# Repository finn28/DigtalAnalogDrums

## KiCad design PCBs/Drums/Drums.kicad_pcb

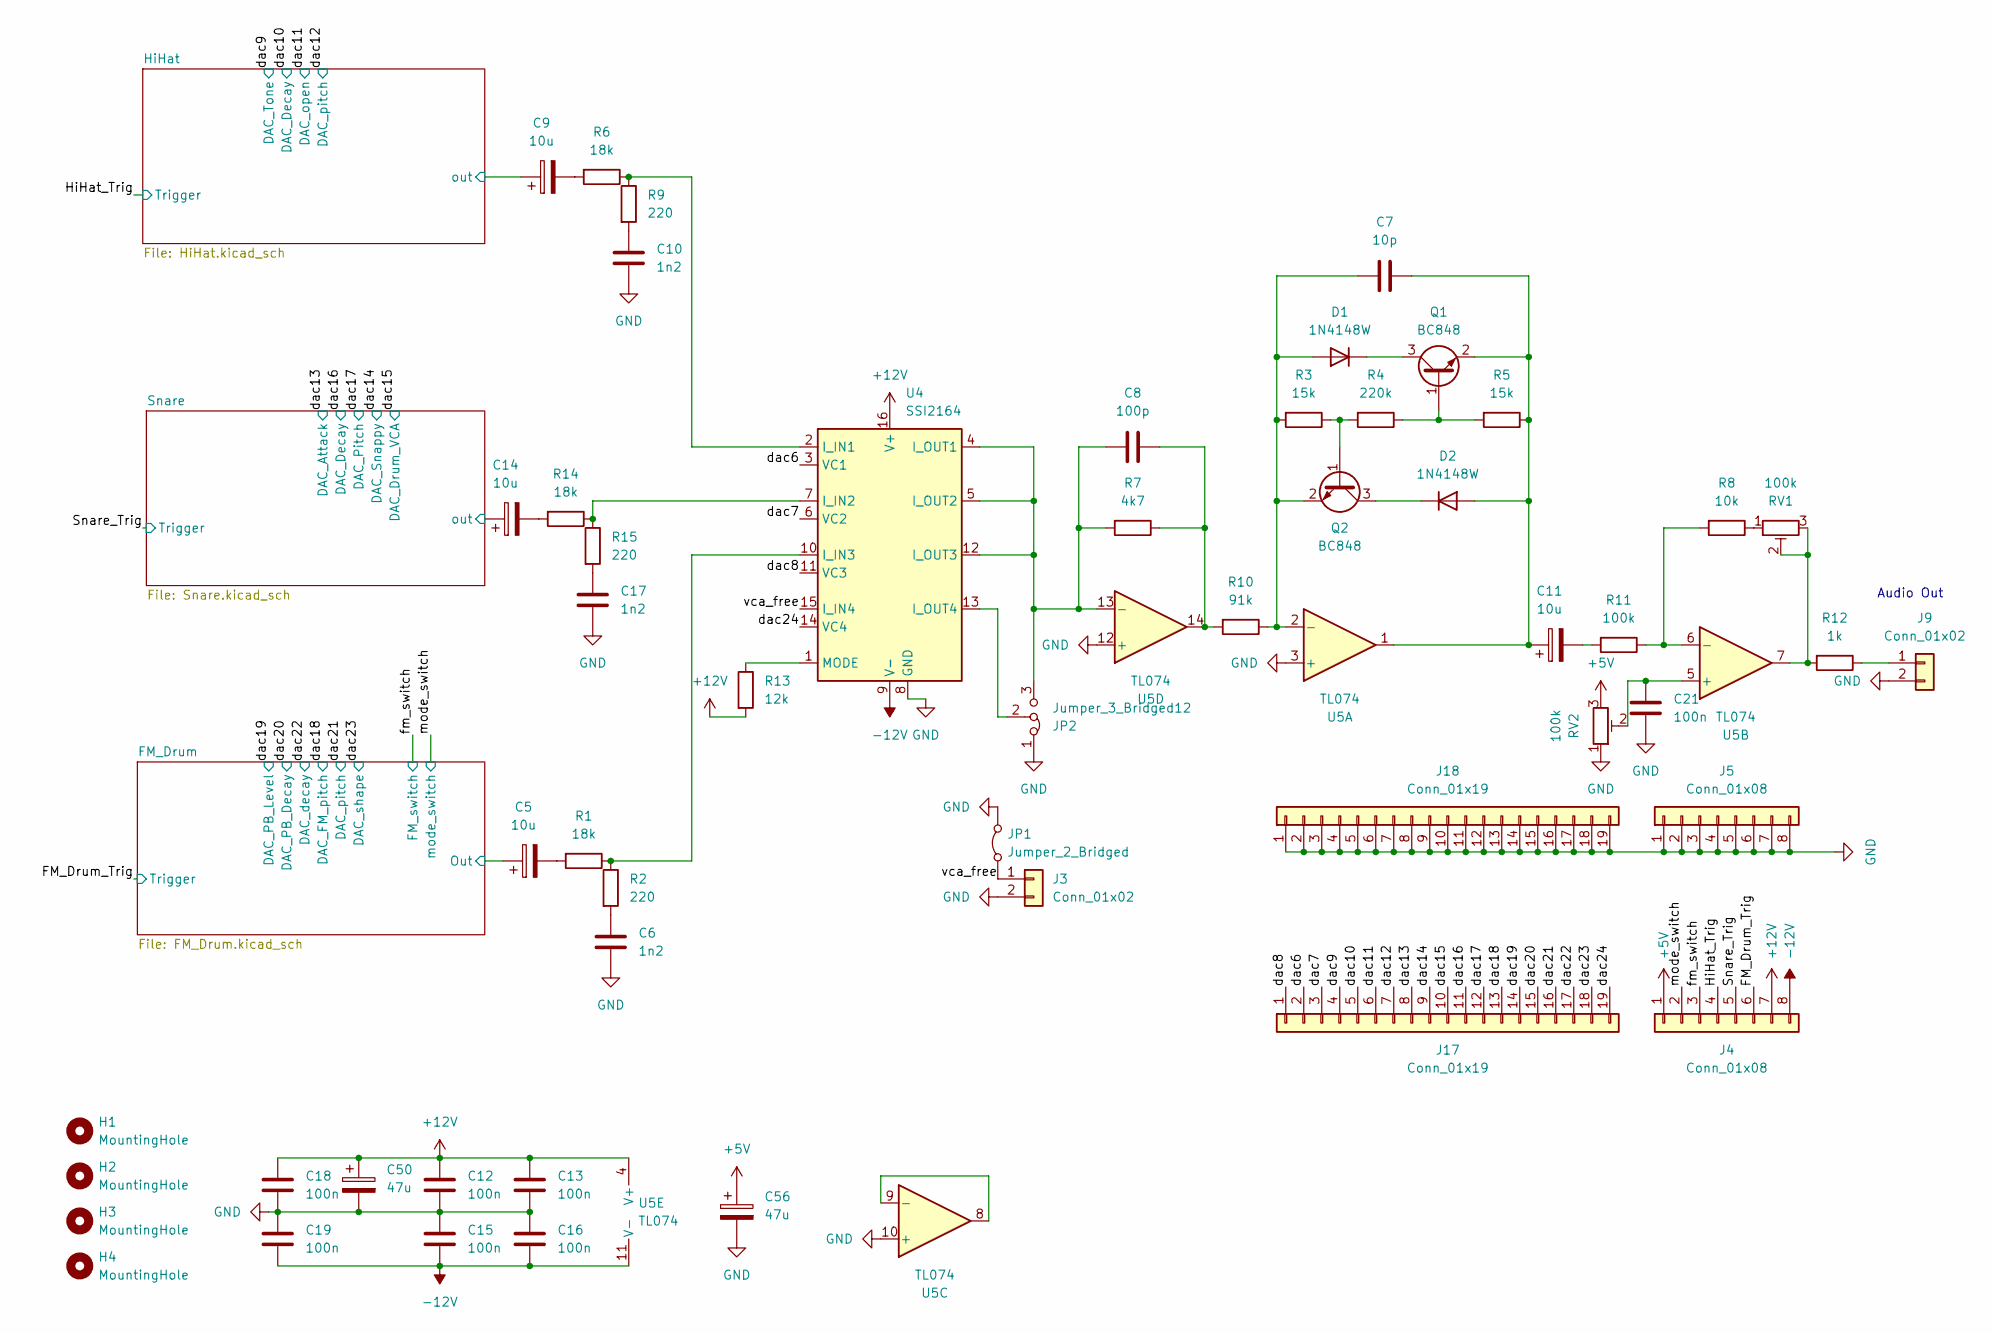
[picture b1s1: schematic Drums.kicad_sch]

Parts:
C5, C9, C11, C14: 10u; CP_Elec_5x5.9
C6, C10, C17: 1n2; C_0805_2012Metric
C7: 10p; C_0805_2012Metric
C8: 100p; C_0805_2012Metric
C12, C13, C15, C16, C18, C19, C21: 100n; C_0402_1005Metric_Pad0.74x0.62mm_HandSolder
C50, C56: 47u; CP_Elec_5x5.9
D1, D2: 1N4148W; D_SOD-123
H1, H2, H3, H4: MountingHole; MountingHole_3.2mm_M3
J3, J9: Conn_01x02; PinHeader_1x02_P2.54mm_Vertical
J4, J5: Conn_01x08; SMD Con8
J17, J18: Conn_01x19; SMD Con19
JP1: Jumper_2_Bridged; SolderJumper-2_P1.3mm_Open_TrianglePad1.0x1.5mm
JP2: Jumper_3_Bridged12; SolderJumper-3_P2.0mm_Open_TrianglePad1.0x1.5mm
Q1, Q2: BC848; SOT-23
R1, R6, R14: 18k; R_0805_2012Metric_Pad1.20x1.40mm_HandSolder
R2, R9, R15: 220; R_0805_2012Metric_Pad1.20x1.40mm_HandSolder
R3, R5: 15k; R_0805_2012Metric_Pad1.20x1.40mm_HandSolder
R4: 220k; R_0805_2012Metric_Pad1.20x1.40mm_HandSolder
R7: 4k7; R_0805_2012Metric_Pad1.20x1.40mm_HandSolder
R8: 10k; R_0805_2012Metric_Pad1.20x1.40mm_HandSolder
R10: 91k; R_0805_2012Metric_Pad1.20x1.40mm_HandSolder
R11: 100k; R_0805_2012Metric_Pad1.20x1.40mm_HandSolder
R12: 1k; R_0805_2012Metric_Pad1.20x1.40mm_HandSolder
R13: 12k; R_0805_2012Metric_Pad1.20x1.40mm_HandSolder
RV1, RV2: 100k; Potentiometer_Bourns_3296W_Vertical
U4: SSI2164; SOIC-16_3.9x9.9mm_P1.27mm
U5: TL074; TSSOP-14_4.4x5mm_P0.65mm

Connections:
+5V: C56.1, J4.1, RV2.3; also elsewhere on the board
+12V: C12.2, C13.2, C18.2, C50.1, J4.7, R13.2, U4.16 (V+), U5.4 (V+); also elsewhere on the board
-12V: C15.1, C16.1, C19.1, J4.8, U4.9 (V-), U5.11 (V-); also elsewhere on the board
/FM_Drum/Out: C5.1; also elsewhere on the board
/FM_Drum_Trig: J4.6; also elsewhere on the board
/HiHat/out: C9.1; also elsewhere on the board
/HiHat_Trig: J4.4; also elsewhere on the board
/Snare/out: C14.1; also elsewhere on the board
/Snare_Trig: J4.5; also elsewhere on the board
/dac6: J17.2, U4.3 (VC1)
/dac7: J17.3, U4.6 (VC2)
/dac8: J17.1, U4.11 (VC3)
/dac9: J17.4; also elsewhere on the board
/dac10: J17.5; also elsewhere on the board
/dac11: J17.6; also elsewhere on the board
/dac12: J17.7; also elsewhere on the board
/dac13: J17.8; also elsewhere on the board
/dac14: J17.9; also elsewhere on the board
/dac15: J17.10; also elsewhere on the board
/dac16: J17.11; also elsewhere on the board
/dac17: J17.12; also elsewhere on the board
/dac18: J17.13; also elsewhere on the board
/dac19: J17.14; also elsewhere on the board
/dac20: J17.15; also elsewhere on the board
/dac21: J17.16; also elsewhere on the board
/dac22: J17.17; also elsewhere on the board
/dac23: J17.18; also elsewhere on the board
/dac24: J17.19, U4.14 (VC4)
/fm_switch: J4.3; also elsewhere on the board
/mode_switch: J4.2; also elsewhere on the board
/vca_free: J3.1, JP1.1 (A), U4.15 (I_IN4)
GND: C6.1, C10.1, C12.1, C13.1, C15.2, C16.2, C17.1, C18.1, C19.2, C21.1, C50.2, C56.2, J3.2, J5.1, J5.2, J5.3, J5.4, J5.5, J5.6, J5.7, J5.8, J9.2, J18.1, J18.2, J18.3, J18.4, J18.5, J18.6, J18.7, J18.8, J18.9, J18.10, J18.11, J18.12, J18.13, J18.14, J18.15, J18.16, J18.17, J18.18, J18.19, JP1.2 (B), JP2.1 (A), RV2.1, U4.8 (GND), U5.3 (+), U5.10 (+), U5.12 (+); also elsewhere on the board
unnamed: C5.2, R1.2
unnamed: C6.2, R2.2
unnamed: C8.2, R7.1, R10.2, U5.14
unnamed: C9.2, R6.2
unnamed: C10.2, R9.2
unnamed: C11.2, R11.2
unnamed: C14.2, R14.2
unnamed: C17.2, R15.2
unnamed: C7.1, D1.2 (A), Q2.2 (E), R3.2, R10.1, U5.2 (-)
unnamed: D1.1 (K), Q1.3 (C)
unnamed: C7.2, C11.1, D2.2 (A), Q1.2 (E), R5.1, U5.1
unnamed: D2.1 (K), Q2.3 (C)
unnamed: J9.1, R12.1
unnamed: C8.1, JP2.3 (B), R7.2, U4.4 (I_OUT1), U4.5 (I_OUT2), U4.12 (I_OUT3), U5.13 (-)
unnamed: JP2.2 (C), U4.13 (I_OUT4)
unnamed: Q1.1 (B), R4.1, R5.2
unnamed: Q2.1 (B), R3.1, R4.2
unnamed: R8.1, RV1.1
unnamed: R12.2, RV1.2, RV1.3, U5.7
unnamed: R6.1, R9.1, U4.2 (I_IN1)
unnamed: R14.1, R15.1, U4.7 (I_IN2)
unnamed: R1.1, R2.1, U4.10 (I_IN3)
unnamed: R13.1, U4.1 (MODE)
unnamed: C21.2, RV2.2, U5.5 (+)
unnamed: R8.2, R11.1, U5.6 (-)
unnamed: U5.8, U5.9 (-)

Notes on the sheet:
Audio Out

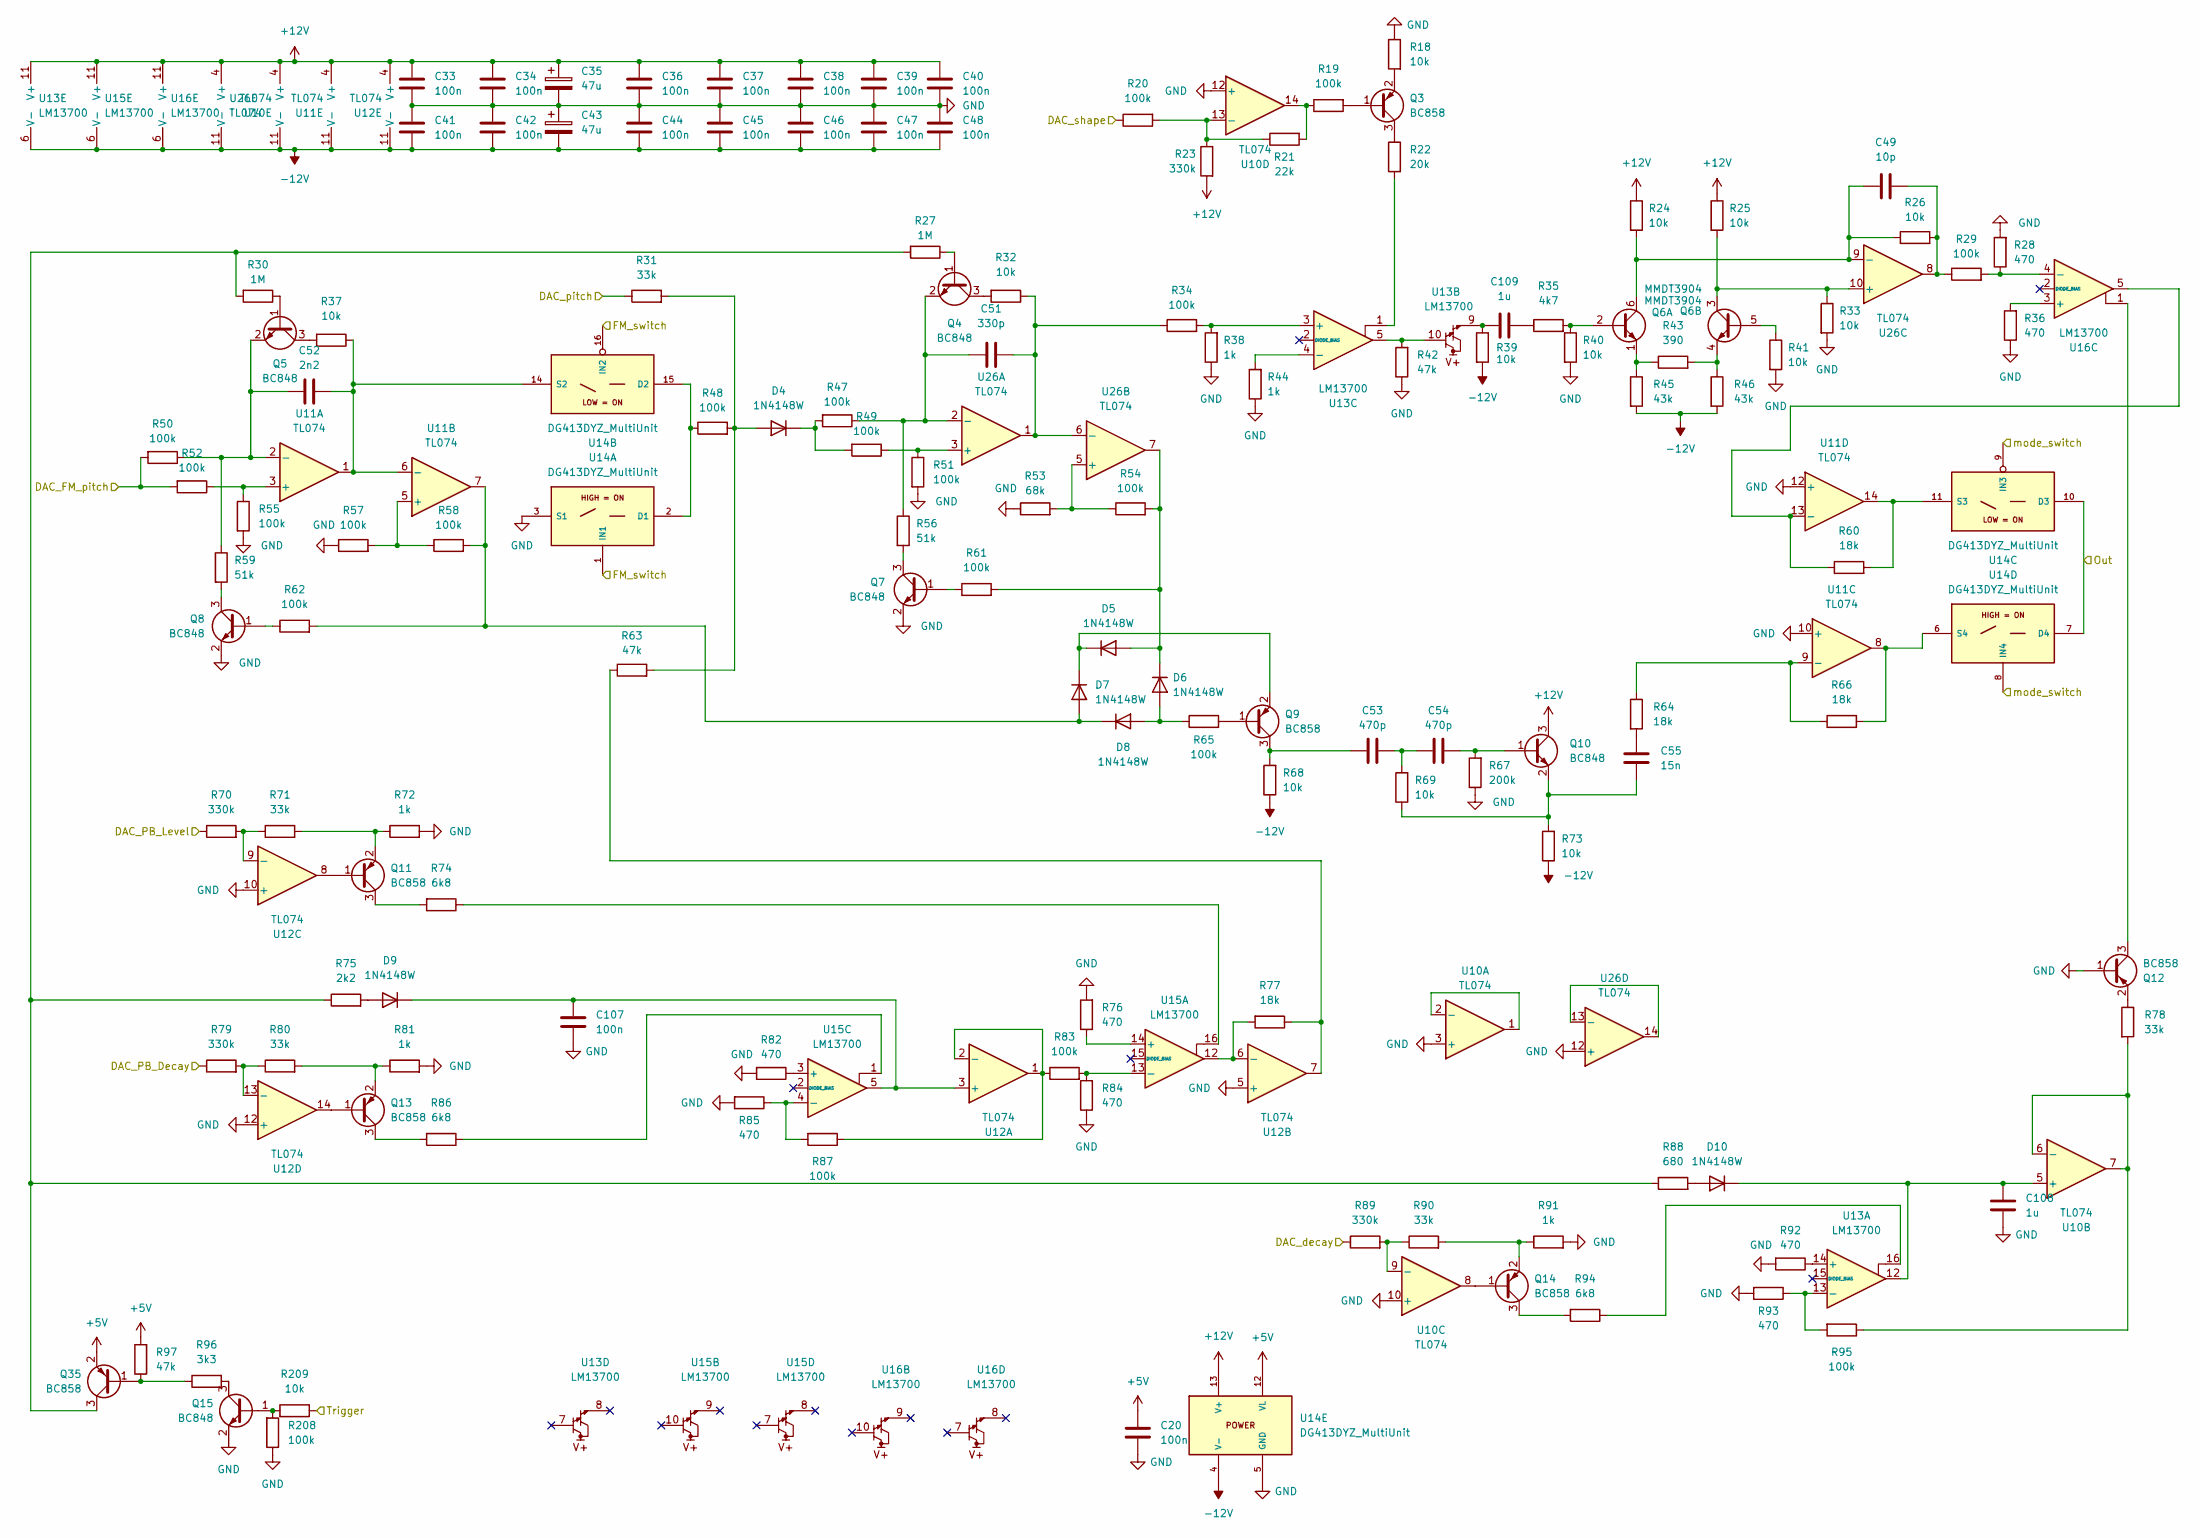
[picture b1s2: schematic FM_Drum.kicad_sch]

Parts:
C20, C33, C34, C36, C37, C38, C39, C40, C41, C42, C44, C45, C46, C47, C48: 100n; C_0402_1005Metric_Pad0.74x0.62mm_HandSolder
C35, C43: 47u; CP_Elec_5x5.9
C49: 10p; C_0805_2012Metric
C51: 330p; C_Rect_L7.2mm_W4.5mm_P5.00mm_FKS2_FKP2_MKS2_MKP2
C52: 2n2; C_Disc_D7.0mm_W2.5mm_P5.00mm
C53, C54: 470p; C_Rect_L7.2mm_W4.5mm_P5.00mm_FKS2_FKP2_MKS2_MKP2
C55: 15n; C_Disc_D7.0mm_W2.5mm_P5.00mm
C107: 100n; C_Rect_L7.2mm_W5.0mm_P5.00mm
C108, C109: 1u; C_Rect_L7.2mm_W5.0mm_P5.00mm
D4, D5, D6, D7, D8, D9, D10: 1N4148W; D_SOD-123
Q3, Q9, Q11, Q12, Q13, Q14, Q35: BC858; SOT-23
Q4, Q5, Q7, Q8, Q10, Q15: BC848; SOT-23
Q6: MMDT3904; SOT-363_SC-70-6
R18, R24, R25, R26, R32, R33, R37, R39, R40, R41, R68, R69, R73, R209: 10k; R_0805_2012Metric_Pad1.20x1.40mm_HandSolder
R19, R20, R29, R34, R47, R48, R49, R50, R51, R52, R54, R55, R57, R58, R61, R62, R65, R83, R87, R95, R208: 100k; R_0805_2012Metric_Pad1.20x1.40mm_HandSolder
R21: 22k; R_0805_2012Metric_Pad1.20x1.40mm_HandSolder
R22: 20k; R_0805_2012Metric_Pad1.20x1.40mm_HandSolder
R23, R70, R79, R89: 330k; R_0805_2012Metric_Pad1.20x1.40mm_HandSolder
R27, R30: 1M; R_0805_2012Metric_Pad1.20x1.40mm_HandSolder
R28, R36, R76, R82, R84, R85, R92, R93: 470; R_0805_2012Metric_Pad1.20x1.40mm_HandSolder
R31, R71, R78, R80, R90: 33k; R_0805_2012Metric_Pad1.20x1.40mm_HandSolder
R35: 4k7; R_0805_2012Metric_Pad1.20x1.40mm_HandSolder
R38, R44, R72, R81, R91: 1k; R_0805_2012Metric_Pad1.20x1.40mm_HandSolder
R42, R63, R97: 47k; R_0805_2012Metric_Pad1.20x1.40mm_HandSolder
R43: 390; R_0805_2012Metric_Pad1.20x1.40mm_HandSolder
R45, R46: 43k; R_0805_2012Metric_Pad1.20x1.40mm_HandSolder
R53: 68k; R_0805_2012Metric_Pad1.20x1.40mm_HandSolder
R56, R59: 51k; R_0805_2012Metric_Pad1.20x1.40mm_HandSolder
R60, R64, R66, R77: 18k; R_0805_2012Metric_Pad1.20x1.40mm_HandSolder
R67: 200k; R_0805_2012Metric_Pad1.20x1.40mm_HandSolder
R74, R86, R94: 6k8; R_0805_2012Metric_Pad1.20x1.40mm_HandSolder
R75: 2k2; R_0805_2012Metric_Pad1.20x1.40mm_HandSolder
R88: 680; R_0805_2012Metric_Pad1.20x1.40mm_HandSolder
R96: 3k3; R_0805_2012Metric_Pad1.20x1.40mm_HandSolder
U10, U11, U12, U26: TL074; TSSOP-14_4.4x5mm_P0.65mm
U13, U15, U16: LM13700; SOIC-16_3.9x9.9mm_P1.27mm
U14: DG413DYZ_MultiUnit; SOIC-16_3.9x9.9mm_P1.27mm; Mouser 968-DG413DYZ

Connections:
+5V: C20.2, Q35.2 (E), R97.2, U14.12 (VL); also elsewhere on the board
+12V: C33.1, C34.1, C35.1, C36.1, C37.1, C38.1, C39.1, C40.1, Q10.3 (C), R23.2, R24.1, R25.1, U10.4 (V+), U11.4 (V+), U12.4 (V+), U13.11 (V+), U14.13 (V+), U15.11 (V+), U16.11 (V+), U26.4 (V+); also elsewhere on the board
-12V: C41.2, C42.2, C43.2, C44.2, C45.2, C46.2, C47.2, C48.2, R39.2, R45.2, R46.2, R68.1, R73.1, U10.11 (V-), U11.11 (V-), U12.11 (V-), U13.6 (V-), U14.4 (V-), U15.6 (V-), U16.6 (V-), U26.11 (V-); also elsewhere on the board
/FM_Drum/Out: U14.7 (D4), U14.10 (D3); also elsewhere on the board
/FM_Drum_Trig: R209.1; also elsewhere on the board
/dac18: R50.2, R52.2; also elsewhere on the board
/dac19: R70.1; also elsewhere on the board
/dac20: R79.1; also elsewhere on the board
/dac21: R31.1; also elsewhere on the board
/dac22: R89.1; also elsewhere on the board
/dac23: R20.1; also elsewhere on the board
/fm_switch: U14.1 (IN1), U14.16 (IN2); also elsewhere on the board
/mode_switch: U14.8 (IN4), U14.9 (IN3); also elsewhere on the board
GND: C20.1, C33.2, C34.2, C35.2, C36.2, C37.2, C38.2, C39.2, C40.2, C41.1, C42.1, C43.1, C44.1, C45.1, C46.1, C47.1, C48.1, C107.2, C108.2, Q7.2 (E), Q8.2 (E), Q12.1 (B), Q15.2 (E), R18.1, R28.2, R33.2, R36.1, R38.1, R40.2, R41.2, R42.1, R44.1, R51.2, R53.1, R55.2, R57.1, R67.1, R72.2, R76.2, R81.2, R82.2, R84.1, R85.2, R91.2, R92.2, R93.2, R208.1, U10.3 (+), U10.10 (+), U10.12 (+), U11.10 (+), U11.12 (+), U12.5 (+), U12.10 (+), U12.12 (+), U14.3 (S1), U14.5 (GND), U26.12 (+); also elsewhere on the board
unnamed: C49.2, R26.2, R29.1, U26.8
unnamed: C53.1, C54.2, R69.2
unnamed: C55.1, R64.2
unnamed: C109.1, R39.1, U13.9
unnamed: C109.2, R35.1
unnamed: D4.2 (A), R31.2, R48.2, R63.2
unnamed: D4.1 (K), R47.2, R49.2
unnamed: D5.2 (A), D6.1 (K), R54.2, R61.2, U26.7
unnamed: D5.1 (K), D7.1 (K), Q9.2 (E)
unnamed: D6.2 (A), D8.2 (A), R65.1
unnamed: D7.2 (A), D8.1 (K), R58.2, R62.2, U11.7
unnamed: D9.2 (A), R75.2
unnamed: C107.1, D9.1 (K), U12.3 (+), U15.5
unnamed: D10.2 (A), R88.2
unnamed: C108.1, D10.1 (K), U10.5 (+), U13.12
unnamed: Q3.1 (B), R19.2
unnamed: Q3.3 (C), R22.1
unnamed: Q3.2 (E), R18.2
unnamed: Q4.1 (B), R27.1
unnamed: Q4.3 (C), R32.2
unnamed: C51.2, Q4.2 (E), R47.1, R56.1, U26.2 (-)
unnamed: Q5.1 (B), R30.1
unnamed: Q5.3 (C), R37.2
unnamed: C52.2, Q5.2 (E), R50.1, R59.1, U11.2 (-)
unnamed: Q6.2 (B1), R35.2, R40.1
unnamed: C49.1, Q6.6 (C1), R24.2, R26.1, U26.9 (-)
unnamed: Q6.1 (E1), R43.1, R45.1
unnamed: Q6.5 (B2), R41.1
unnamed: Q6.3 (C2), R25.2, R33.1, U26.10 (+)
unnamed: Q6.4 (E2), R43.2, R46.1
unnamed: Q7.1 (B), R61.1
unnamed: Q7.3 (C), R56.2
unnamed: Q8.1 (B), R62.1
unnamed: Q8.3 (C), R59.2
unnamed: Q9.1 (B), R65.2
unnamed: C53.2, Q9.3 (C), R68.2
unnamed: C54.1, Q10.1 (B), R67.2
unnamed: C55.2, Q10.2 (E), R69.1, R73.2
unnamed: Q11.1 (B), U12.8
unnamed: Q11.3 (C), R74.2
unnamed: Q11.2 (E), R71.2, R72.1
unnamed: Q12.3 (C), U16.1
unnamed: Q12.2 (E), R78.1
unnamed: Q13.1 (B), U12.14
unnamed: Q13.3 (C), R86.2
unnamed: Q13.2 (E), R80.2, R81.1
unnamed: Q14.1 (B), U10.8
unnamed: Q14.3 (C), R94.2
unnamed: Q14.2 (E), R90.2, R91.1
unnamed: Q15.1 (B), R208.2, R209.2
unnamed: Q15.3 (C), R96.2
unnamed: Q35.1 (B), R96.1, R97.1
unnamed: Q35.3 (C), R27.2, R30.2, R75.1, R88.1
unnamed: R19.1, R21.2, U10.14
unnamed: R22.2, U13.1
unnamed: R42.2, U13.5, U13.10
unnamed: R63.1, R77.1, U12.7
unnamed: R74.1, U15.16
unnamed: R86.1, U15.1
unnamed: R94.1, U13.16
unnamed: U10.1, U10.2 (-)
unnamed: R78.2, R95.1, U10.6 (-), U10.7
unnamed: R89.2, R90.1, U10.9 (-)
unnamed: R20.2, R21.1, R23.1, U10.13 (-)
unnamed: R52.1, R55.1, U11.3 (+)
unnamed: R57.2, R58.1, U11.5 (+)
unnamed: C52.1, R37.1, U11.1, U11.6 (-), U14.14 (S2)
unnamed: R64.1, R66.1, U11.9 (-)
unnamed: R60.1, U11.13 (-), U16.5
unnamed: R83.1, R87.1, U12.1, U12.2 (-)
unnamed: R77.2, U12.6 (-), U15.12
unnamed: R70.2, R71.1, U12.9 (-)
unnamed: R79.2, R80.1, U12.13 (-)
unnamed: R92.1, U13.14 (+)
unnamed: R93.1, R95.2, U13.13 (-)
unnamed: R34.2, R38.2, U13.3 (+)
unnamed: R44.2, U13.4 (-)
unnamed: R48.1, U14.2 (D1), U14.15 (D2)
unnamed: R60.2, U11.14, U14.11 (S3)
unnamed: R66.2, U11.8, U14.6 (S4)
unnamed: R76.1, U15.14 (+)
unnamed: R83.2, R84.2, U15.13 (-)
unnamed: R82.1, U15.3 (+)
unnamed: R85.1, R87.2, U15.4 (-)
unnamed: R36.2, U16.3 (+)
unnamed: R28.1, R29.2, U16.4 (-)
unnamed: R49.1, R51.1, U26.3 (+)
unnamed: R53.2, R54.1, U26.5 (+)
unnamed: C51.1, R32.1, R34.1, U26.1, U26.6 (-)
unnamed: U26.13 (-), U26.14

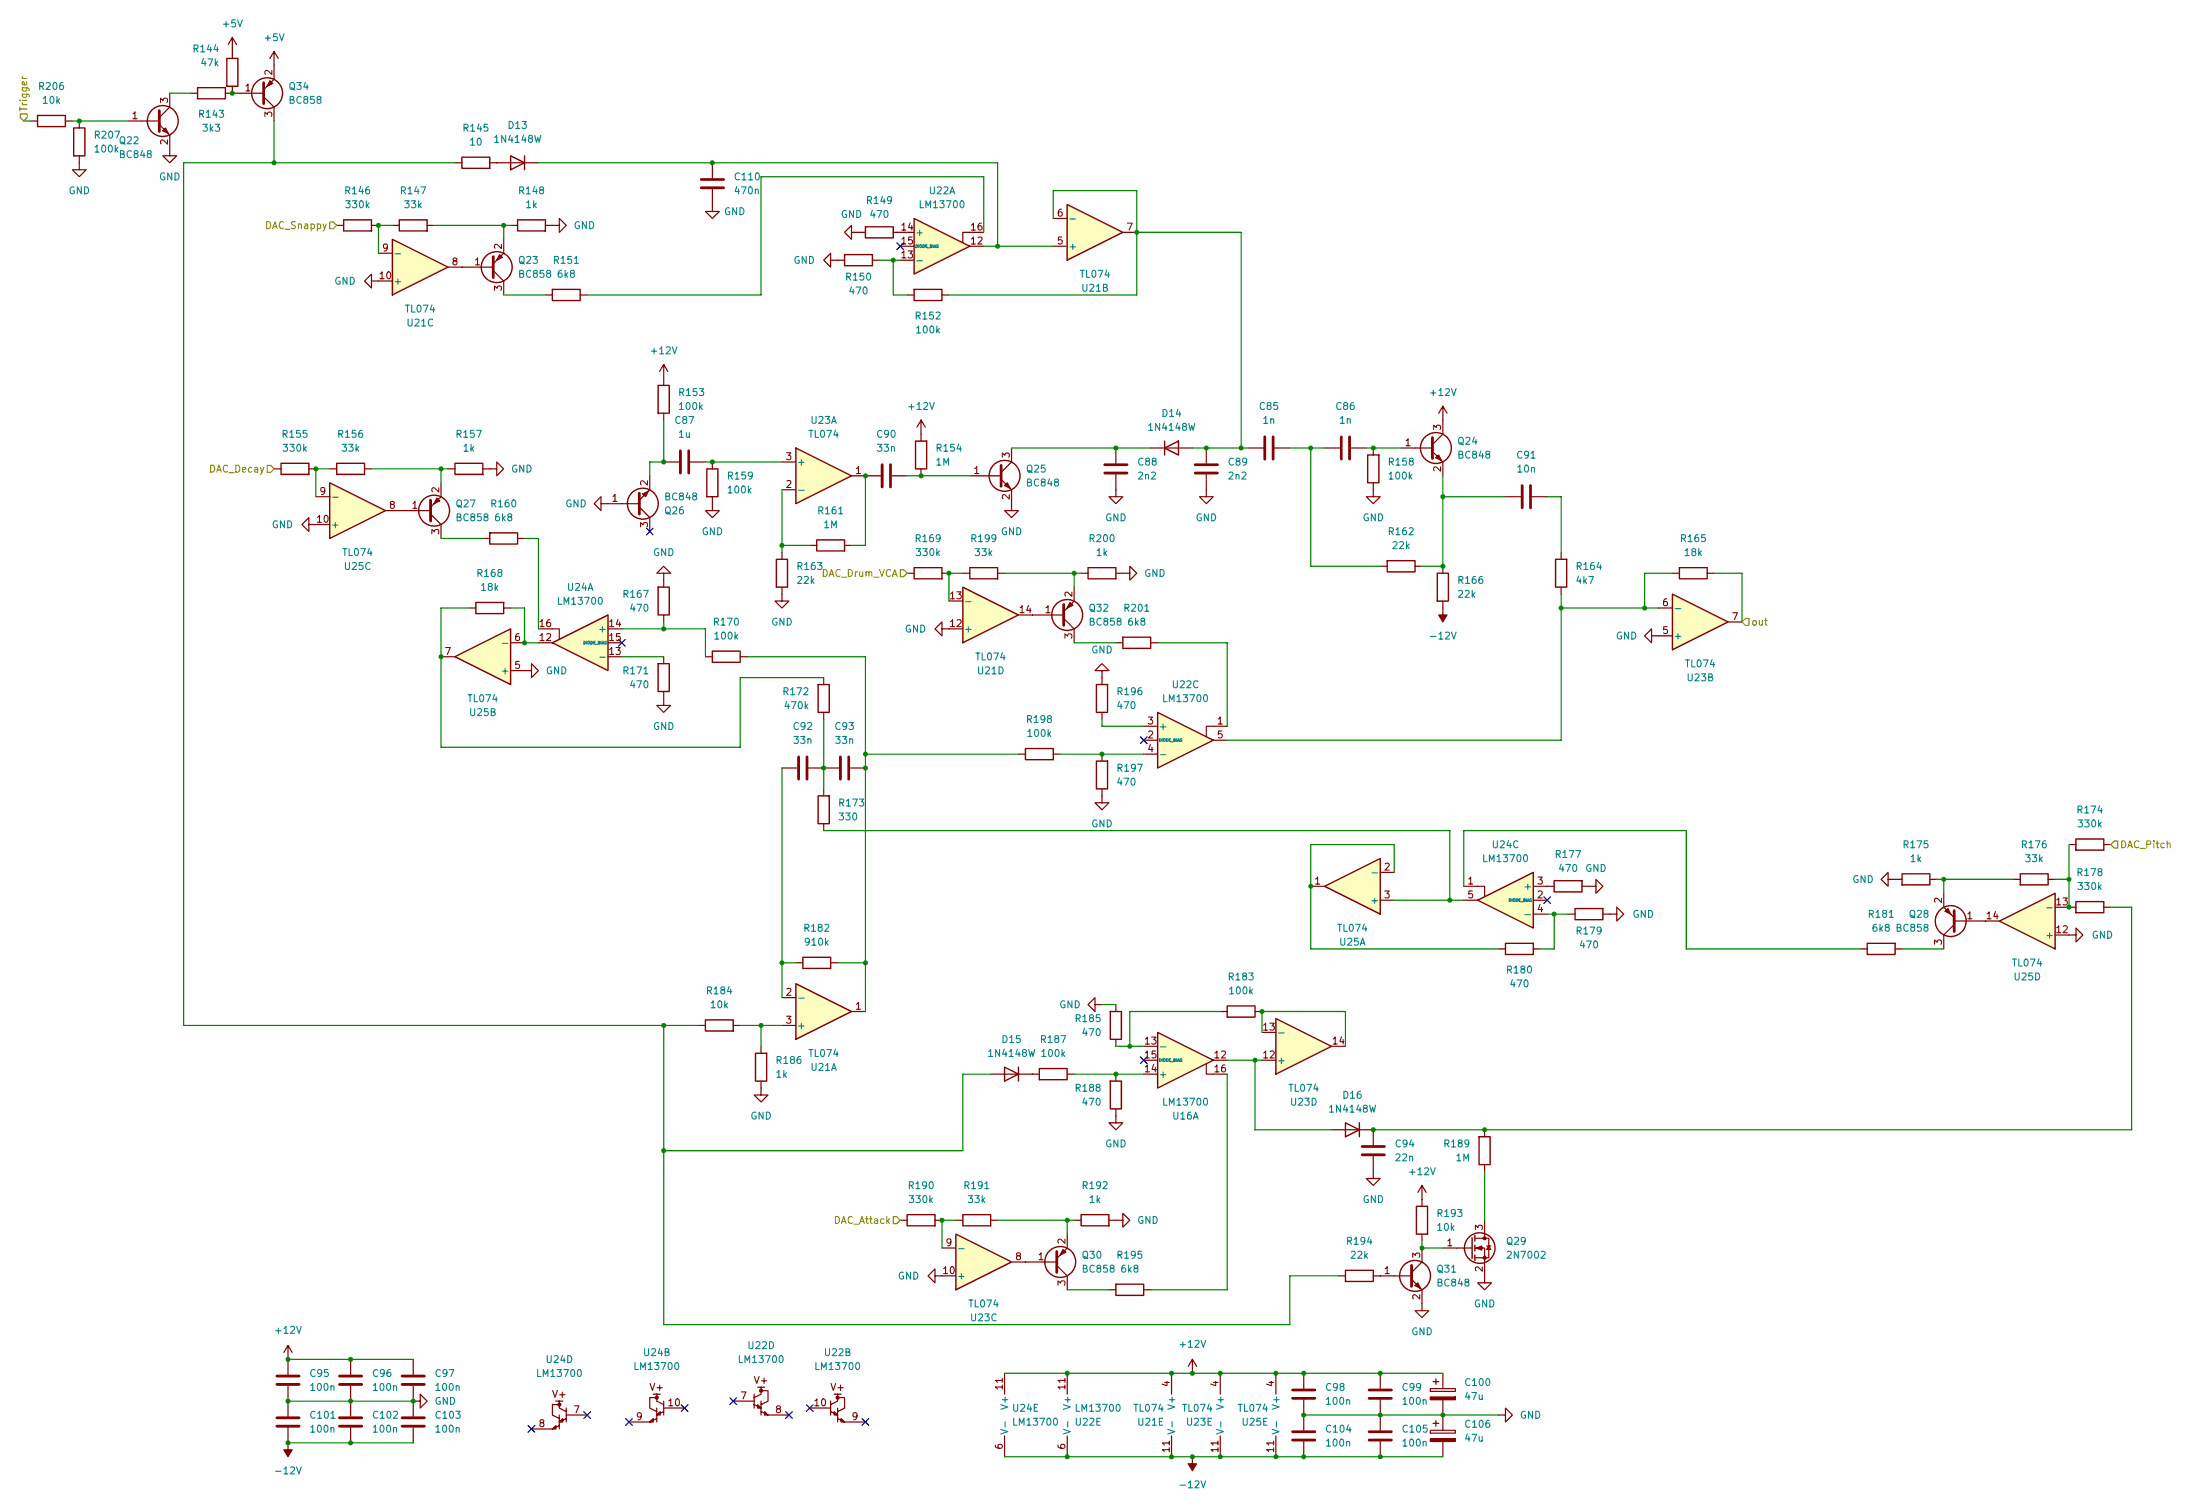
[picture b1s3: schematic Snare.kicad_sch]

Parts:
C85, C86: 1n; C_Disc_D7.0mm_W2.5mm_P5.00mm
C87: 1u; C_Rect_L7.2mm_W5.0mm_P5.00mm
C88, C89: 2n2; C_Disc_D7.0mm_W2.5mm_P5.00mm
C90, C92, C93: 33n; C_Disc_D7.0mm_W2.5mm_P5.00mm
C91: 10n; C_Disc_D7.0mm_W2.5mm_P5.00mm
C94: 22n; C_Disc_D7.0mm_W2.5mm_P5.00mm
C95, C96, C97, C98, C99, C101, C102, C103, C104, C105: 100n; C_0402_1005Metric_Pad0.74x0.62mm_HandSolder
C100, C106: 47u; CP_Elec_5x5.9
C110: 470n; C_Rect_L7.2mm_W5.0mm_P5.00mm
D13, D14, D15, D16: 1N4148W; D_SOD-123
Q22, Q24, Q25, Q26, Q31: BC848; SOT-23
Q23, Q27, Q28, Q30, Q32, Q34: BC858; SOT-23
Q29: 2N7002; SOT-23
R143: 3k3; R_0805_2012Metric_Pad1.20x1.40mm_HandSolder
R144: 47k; R_0805_2012Metric_Pad1.20x1.40mm_HandSolder
R145: 10; R_0805_2012Metric_Pad1.20x1.40mm_HandSolder
R146, R155, R169, R174, R178, R190: 330k; R_0805_2012Metric_Pad1.20x1.40mm_HandSolder
R147, R156, R176, R191, R199: 33k; R_0805_2012Metric_Pad1.20x1.40mm_HandSolder
R148, R157, R175, R186, R192, R200: 1k; R_0805_2012Metric_Pad1.20x1.40mm_HandSolder
R149, R150, R167, R171, R177, R179, R180, R185, R188, R196, R197: 470; R_0805_2012Metric_Pad1.20x1.40mm_HandSolder
R151, R160, R181, R195, R201: 6k8; R_0805_2012Metric_Pad1.20x1.40mm_HandSolder
R152, R153, R158, R159, R170, R183, R187, R198, R207: 100k; R_0805_2012Metric_Pad1.20x1.40mm_HandSolder
R154, R161, R189: 1M; R_0805_2012Metric_Pad1.20x1.40mm_HandSolder
R162, R163, R166, R194: 22k; R_0805_2012Metric_Pad1.20x1.40mm_HandSolder
R164: 4k7; R_0805_2012Metric_Pad1.20x1.40mm_HandSolder
R165, R168: 18k; R_0805_2012Metric_Pad1.20x1.40mm_HandSolder
R172: 470k; R_0805_2012Metric_Pad1.20x1.40mm_HandSolder
R173: 330; R_0805_2012Metric_Pad1.20x1.40mm_HandSolder
R182: 910k; R_0805_2012Metric_Pad1.20x1.40mm_HandSolder
R184, R193, R206: 10k; R_0805_2012Metric_Pad1.20x1.40mm_HandSolder
U16, U22, U24: LM13700; SOIC-16_3.9x9.9mm_P1.27mm
U21, U23, U25: TL074; TSSOP-14_4.4x5mm_P0.65mm

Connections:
+5V: Q34.2 (E), R144.1; also elsewhere on the board
+12V: C95.1, C96.1, C97.1, C98.1, C99.1, C100.1, Q24.3 (C), R153.1, R154.2, R193.1, U21.4 (V+), U22.11 (V+), U23.4 (V+), U24.11 (V+), U25.4 (V+); also elsewhere on the board
-12V: C101.2, C102.2, C103.2, C104.2, C105.2, C106.2, R166.2, U21.11 (V-), U22.6 (V-), U23.11 (V-), U24.6 (V-), U25.11 (V-); also elsewhere on the board
/Snare/out: R165.1, U23.7; also elsewhere on the board
/Snare_Trig: R206.2; also elsewhere on the board
/dac13: R190.1; also elsewhere on the board
/dac14: R146.1; also elsewhere on the board
/dac15: R169.1; also elsewhere on the board
/dac16: R155.1; also elsewhere on the board
/dac17: R174.1; also elsewhere on the board
GND: C88.1, C89.1, C94.1, C95.2, C96.2, C97.2, C98.2, C99.2, C100.2, C101.1, C102.1, C103.1, C104.1, C105.1, C106.1, C110.2, Q22.2 (E), Q25.2 (E), Q26.1 (B), Q29.2 (S), Q31.2 (E), R148.2, R149.2, R150.2, R157.2, R158.1, R159.2, R163.2, R167.2, R171.1, R175.2, R177.2, R179.2, R185.2, R186.1, R188.1, R192.2, R196.2, R197.1, R200.2, R207.2, U21.10 (+), U21.12 (+), U23.5 (+), U23.10 (+), U25.5 (+), U25.10 (+), U25.12 (+); also elsewhere on the board
unnamed: C85.1, C86.2, R162.2
unnamed: C90.1, R161.2, U23.1
unnamed: C91.1, R164.2
unnamed: C92.2, C93.1, R172.1, R173.2
unnamed: C93.2, R170.1, R182.2, R198.1, U21.1
unnamed: D13.2 (A), R145.2
unnamed: C110.1, D13.1 (K), U21.5 (+), U22.12
unnamed: C85.2, C89.2, D14.2 (A), R152.1, U21.6 (-), U21.7
unnamed: C88.2, D14.1 (K), Q25.3 (C)
unnamed: D15.2 (A), Q34.3 (C), R145.1, R184.1, R194.2
unnamed: D15.1 (K), R187.2
unnamed: D16.2 (A), U16.12, U23.12 (+)
unnamed: C94.2, D16.1 (K), R178.1, R189.2
unnamed: Q22.1 (B), R206.1, R207.1
unnamed: Q22.3 (C), R143.2
unnamed: Q23.1 (B), U21.8
unnamed: Q23.3 (C), R151.2
unnamed: Q23.2 (E), R147.2, R148.1
unnamed: C86.1, Q24.1 (B), R158.2
unnamed: C91.2, Q24.2 (E), R162.1, R166.1
unnamed: C90.2, Q25.1 (B), R154.1
unnamed: C87.1, Q26.2 (E), R153.2
unnamed: Q27.1 (B), U25.8
unnamed: Q27.3 (C), R160.2
unnamed: Q27.2 (E), R156.2, R157.1
unnamed: Q28.1 (B), U25.14
unnamed: Q28.3 (C), R181.2
unnamed: Q28.2 (E), R175.1, R176.2
unnamed: Q29.3 (D), R189.1
unnamed: Q29.1 (G), Q31.3 (C), R193.2
unnamed: Q30.1 (B), U23.8
unnamed: Q30.3 (C), R195.2
unnamed: Q30.2 (E), R191.2, R192.1
unnamed: Q31.1 (B), R194.1
unnamed: Q32.1 (B), U21.14
unnamed: Q32.3 (C), R201.2
unnamed: Q32.2 (E), R199.2, R200.1
unnamed: Q34.1 (B), R143.1, R144.2
unnamed: R151.1, U22.16
unnamed: R160.1, U24.16
unnamed: R168.1, R172.2, U25.7
unnamed: R181.1, U24.1
unnamed: R195.1, U16.16
unnamed: R201.1, U22.1
unnamed: R187.1, R188.2, U16.14 (+)
unnamed: R183.2, R185.1, U16.13 (-)
unnamed: R184.2, R186.2, U21.3 (+)
unnamed: C92.1, R182.1, U21.2 (-)
unnamed: R146.2, R147.1, U21.9 (-)
unnamed: R169.2, R199.1, U21.13 (-)
unnamed: R149.1, U22.14 (+)
unnamed: R150.1, R152.2, U22.13 (-)
unnamed: R196.1, U22.3 (+)
unnamed: R197.2, R198.2, U22.4 (-)
unnamed: C87.2, R159.1, U23.3 (+)
unnamed: R161.1, R163.1, U23.2 (-)
unnamed: R164.1, R165.2, U22.5, U23.6 (-)
unnamed: R190.2, R191.1, U23.9 (-)
unnamed: R183.1, U23.13 (-), U23.14
unnamed: R167.1, R170.2, U24.14 (+)
unnamed: R171.2, U24.13 (-)
unnamed: R177.1, U24.3 (+)
unnamed: R179.1, R180.2, U24.4 (-)
unnamed: R173.1, U24.5, U25.3 (+)
unnamed: R180.1, U25.1, U25.2 (-)
unnamed: R168.2, U24.12, U25.6 (-)
unnamed: R155.2, R156.1, U25.9 (-)
unnamed: R174.2, R176.1, R178.2, U25.13 (-)
